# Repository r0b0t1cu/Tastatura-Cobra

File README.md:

# [RO] Tastatură Custom pentru Cobra & ZX Spectrum  

Acesta este un proiect open-source pentru o tastatură mecanică compatibilă cu computerul românesc **Cobra** și alte clone **ZX Spectrum**.
Tastatura a fost proiectată pentru a fi ușor de construit, utilizând componente accesibile.  

## Caracteristici  
- **Compatibilitate:** Cobra, ZX Spectrum și clone  
- **Conexiune:** Cablu panglică 2x10, conector montat pe partea inferioară a PCB-ului
- **Componente principale:**  
  - 59 Switch-uri mecanice cu 3 pini din plastic  
  - 3 x **IC CD4066**  
  - 29 x **diode BAT42**  
  - 12 x **rezistențe 100k**  
  - 1 x **condensator 10uF**  
  - 3 x **condensator 100nF**  
  - 1 x **conector 2x10 pini**  
  - optional - 1 x **conector 2x4 pini**
- **Funcționalitate extinsă:**
  - Taste speciale pentru CP/M pe Cobra
  - Taste separate pentru: del, cursor, caps lock, edit, extended mode, "." (punct), "," (virgula), ":" (doua puncte)

## Instalare și Conectare  
1. **Montaj PCB:** Conectorul cablului panglică **trebuie montat pe partea inferioară** a PCB-ului.  
2. **Pentru Cobra:** Se conectează direct la interfața tastaturii.  
3. **Pentru ZX Spectrum și clone:** Se identifică manual liniile și coloanele din matrice și se ajustează conexiunile corespunzător. 
4. Tastatura este gândită să se potrivească pe carcasa de aici:
   - [https://www.z80-romania.ro/CoBra-64](https://www.z80-romania.ro/CoBra-64)  
   - Fișiere: [Download CoBra Case (ZIP)](https://www.z80-romania.ro/files/64/Carcasa%20CoBra%20-%20cobrasov.com%20(2024).zip?1708896374)

## Fișiere Disponibile  
- **Schematica și PCB:** Fișiere KiCad în folderul KICAD
- **Fișiere Gerber:** Pentru fabricarea PCB-ului în folderul PRODUCTION
- **BOM:** În folderul BOM
- **Grafica pentru stickere taste:** În folderul PDF
- **Schema:** În folderul PDF

## Surse și Mulțumiri  
Informațiile din acest proiect au fost inspirate și dezvoltate pe baza resurselor de la:  
- [cobrasov.com](https://cobrasov.com)  
- [CherryZXKeyboard](https://github.com/VlastimilWagner/CherryZXKeyboard)
- Și cu observații și input prețios de la [svpantazi](https://github.com/svpantazi)  

## Licență  
Acest proiect este **complet liber** pentru oricine dorește să-l folosească, modifice sau îmbunătățească.

# [EN] Custom Keyboard for Cobra & ZX Spectrum  

This is an open-source project for a mechanical keyboard compatible with the Romanian **Cobra** computer and other **ZX Spectrum clones**.  
The keyboard is designed to be easy to build, using readily available components.  

## Features  
- **Compatibility:** Cobra, ZX Spectrum, and clones  
- **Connection:** 2x10 ribbon cable, connector mounted on the **bottom side** of the PCB  
- **Main components:**  
  - 59 **mechanical switches** (3-pin plastic)  
  - 3 x **IC CD4066**  
  - 29 x **BAT42 diodes**  
  - 12 x **100k resistors**  
  - 1 x **10µF capacitor**  
  - 3 x **100nF capacitors**  
  - 1 x **2x10-pin connector**  
  - Optional: 1 x **2x4-pin connector**  
- **Extended functionality:**  
  - Special keys for CP/M on Cobra  
  - Separate keys for: Delete, Cursor, Caps Lock, Edit, Extended Mode, ".", ",", ":"  

## Installation & Connection  
1. **PCB Assembly:** The ribbon cable **must be mounted on the bottom side** of the PCB.  
2. **For Cobra:** Connects directly to the keyboard interface.  
3. **For ZX Spectrum and clones:** Manually identify the matrix rows and columns and adjust the connections accordingly.  
4. The keyboard is designed to fit in the case from:  
   - [https://www.z80-romania.ro/CoBra-64](https://www.z80-romania.ro/CoBra-64)  
   - Case files: [Download CoBra Case (ZIP)](https://www.z80-romania.ro/files/64/Carcasa%20CoBra%20-%20cobrasov.com%20(2024).zip?1708896374)

## Available Files  
- **Schematics & PCB:** KiCad files in the **KICAD** folder  
- **Gerber Files:** For PCB fabrication in the **PRODUCTION** folder  
- **BOM (Bill of Materials):** Located in the **BOM** folder  
- **Keycap Sticker Graphics:** In the **PDF** folder  
- **Schematic Diagram:** In the **PDF** folder  

## Sources & Acknowledgments  
This project was inspired and developed using information from:  
- [cobrasov.com](https://cobrasov.com)  
- [CherryZXKeyboard](https://github.com/VlastimilWagner/CherryZXKeyboard)  
- With valuable insights and feedback from [svpantazi](https://github.com/svpantazi)  

## License  
This project is **completely free** for anyone to use, modify, or improve.

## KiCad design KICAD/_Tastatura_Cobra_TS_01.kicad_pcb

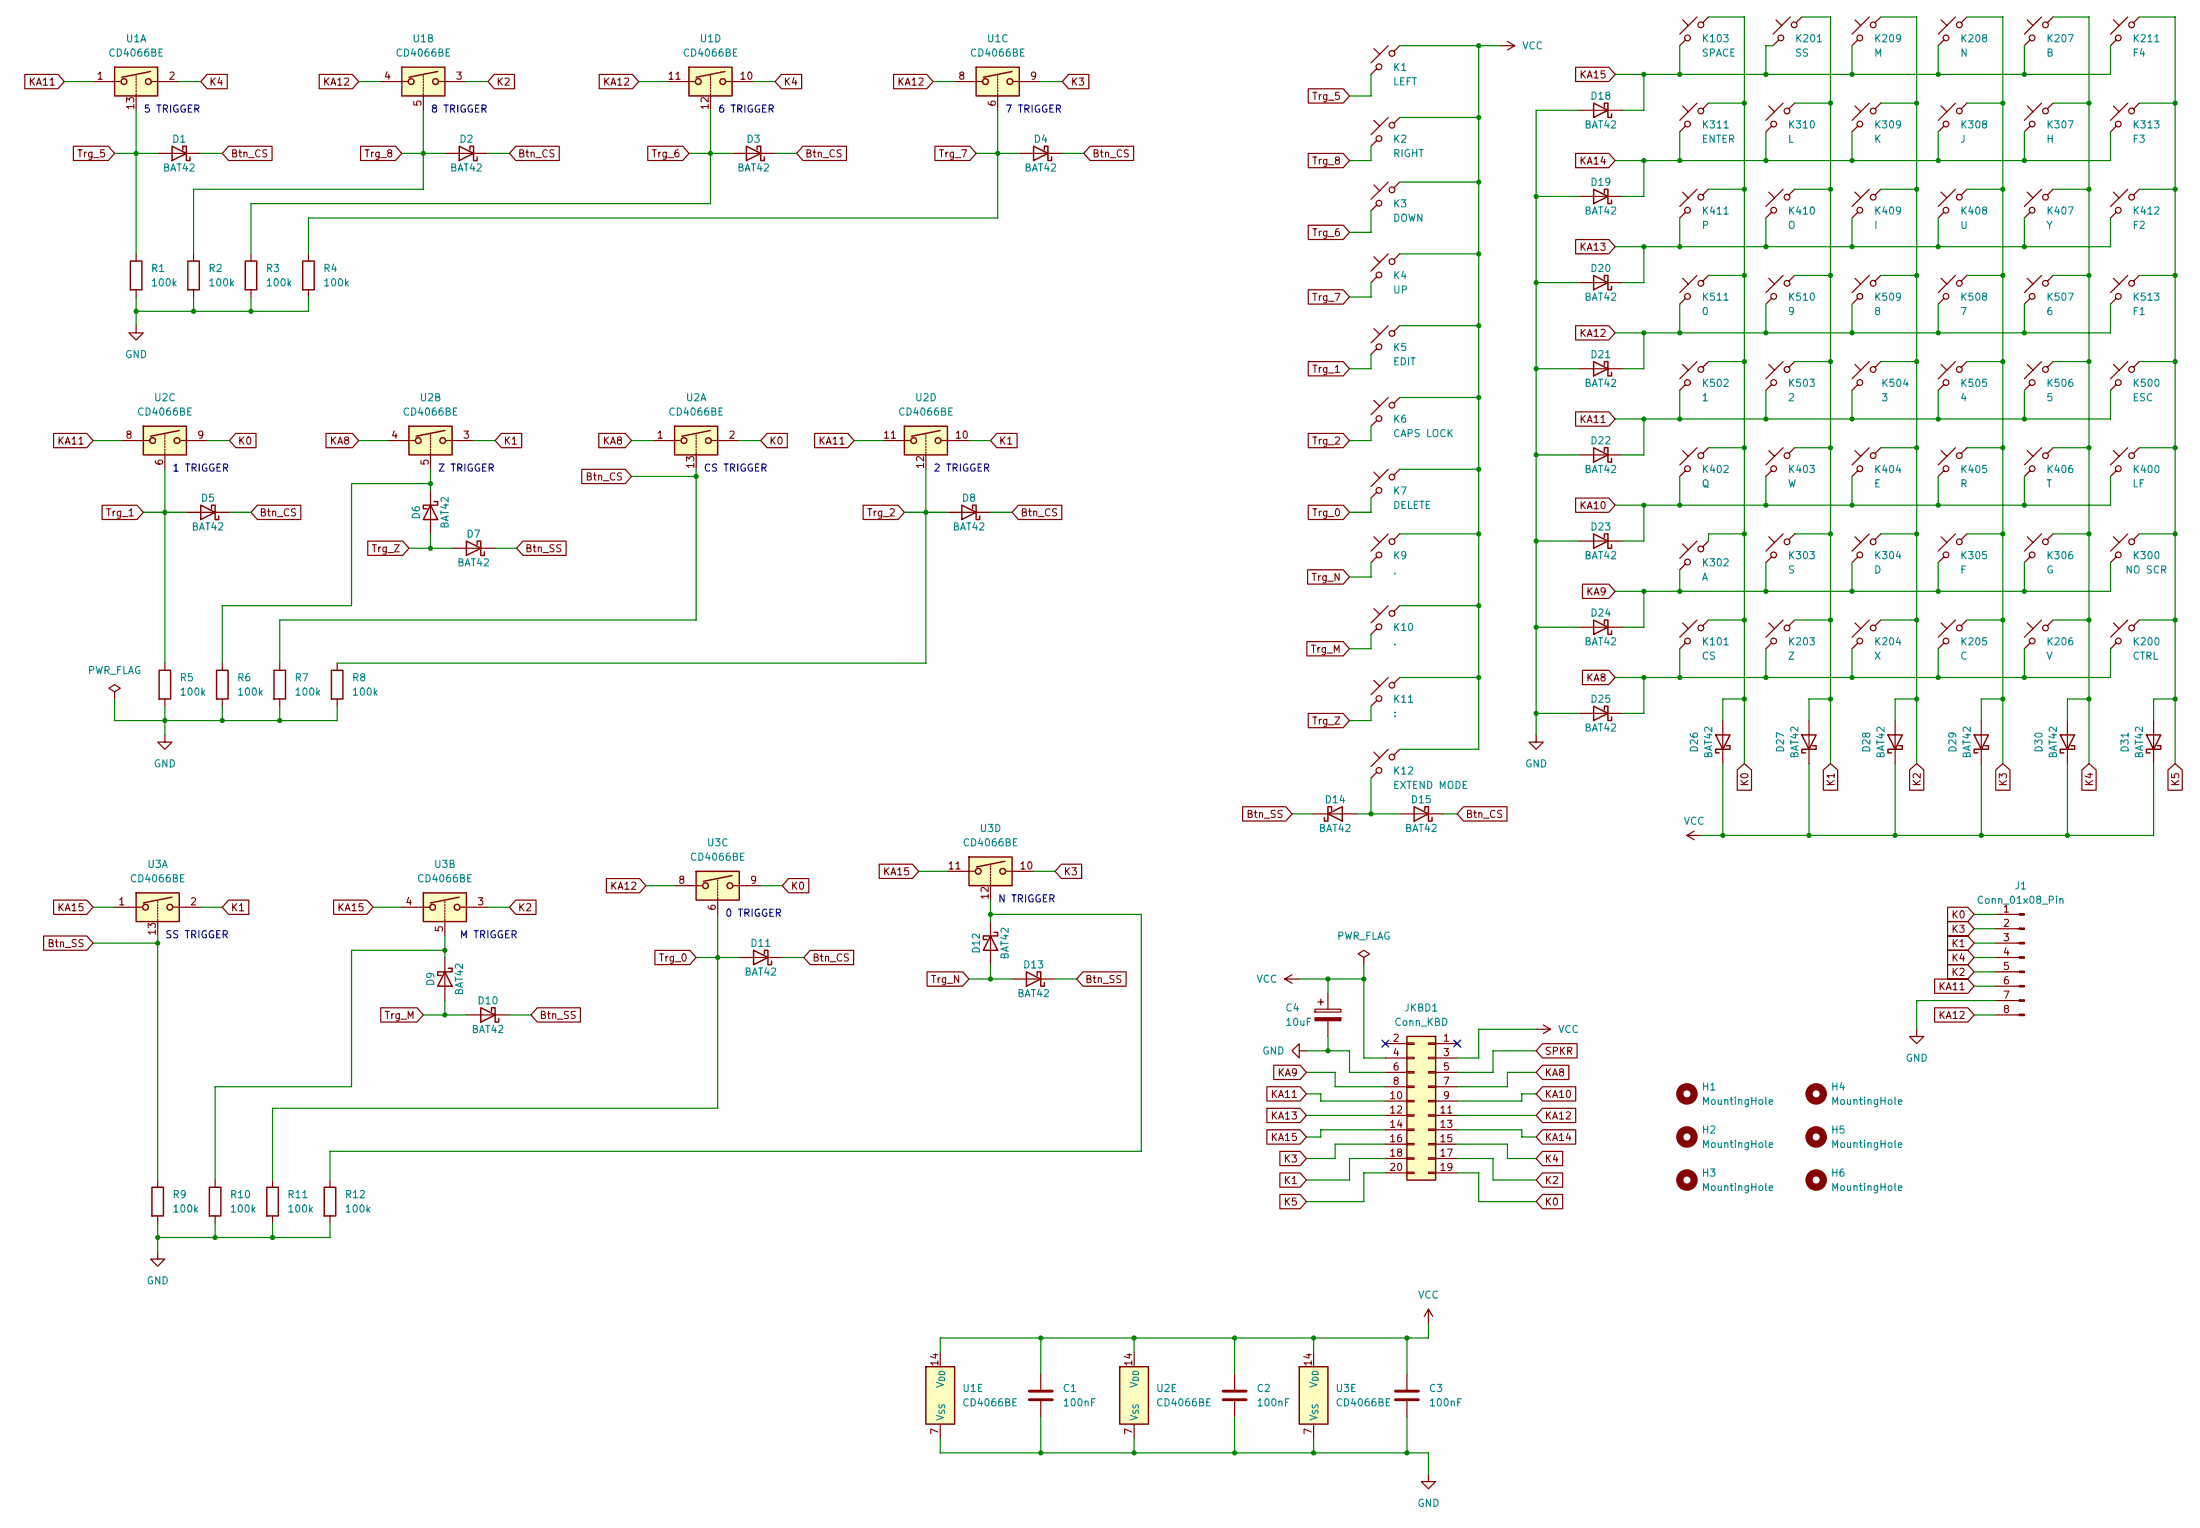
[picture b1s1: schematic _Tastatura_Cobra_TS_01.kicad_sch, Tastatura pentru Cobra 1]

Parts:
C1, C2, C3: 100nF; C_Disc_D4.3mm_W1.9mm_P5.00mm
C4: 10uF; CP_Radial_D5.0mm_P2.50mm
D1, D2, D3, D4, D5, D6, D7, D8, D9, D10, D11, D12, D13, D14, D15, D18, D19, D20, D21, D22, D23, D24, D25, D26, D27, D28, D29, D30, D31: BAT42; D_DO-35_SOD27_P7.62mm_Horizontal
H1, H2, H3, H4, H5, H6: MountingHole; MountingHole_3.2mm_M3_Pad_TopBottom
J1: Conn_01x08_Pin; PinHeader_2x04_P2.54mm_Horizontal
JKBD1: Conn_KBD; IDC-Header_2x10_P2.54mm_Horizontal
K1: LEFT; SW_Cherry_MX_1.00u_PCB
K2: RIGHT; SW_Cherry_MX_1.00u_PCB
K3: DOWN; SW_Cherry_MX_1.25u_PCB
K4: UP; SW_Cherry_MX_1.25u_PCB
K5: EDIT; SW_Cherry_MX_1.25u_PCB
K6: CAPS LOCK; SW_Cherry_MX_1.25u_PCB
K7: DELETE; SW_Cherry_MX_1.25u_PCB
K9: ,; SW_Cherry_MX_1.25u_PCB
K10: .; SW_Cherry_MX_1.00u_PCB
K11: :; SW_Cherry_MX_1.00u_PCB
K12: EXTEND MODE; SW_Cherry_MX_1.00u_PCB
K101: CS; SW_Cherry_MX_2.00u_PCB
K103: SPACE; SW_Cherry_MX_6.25u_PCB
K200: CTRL; SW_Cherry_MX_1.00u_PCB
K201: SS; SW_Cherry_MX_2.00u_PCB
K203: Z; SW_Cherry_MX_1.00u_PCB
K204: X; SW_Cherry_MX_1.00u_PCB
K205: C; SW_Cherry_MX_1.00u_PCB
K206: V; SW_Cherry_MX_1.00u_PCB
K207: B; SW_Cherry_MX_1.00u_PCB
K208: N; SW_Cherry_MX_1.00u_PCB
K209: M; SW_Cherry_MX_1.00u_PCB
K211: F4; SW_Cherry_MX_1.00u_PCB
K300: NO SCR; SW_Cherry_MX_1.00u_PCB
K302: A; SW_Cherry_MX_1.00u_PCB
K303: S; SW_Cherry_MX_1.00u_PCB
K304: D; SW_Cherry_MX_1.00u_PCB
K305: F; SW_Cherry_MX_1.00u_PCB
K306: G; SW_Cherry_MX_1.00u_PCB
K307: H; SW_Cherry_MX_1.00u_PCB
K308: J; SW_Cherry_MX_1.00u_PCB
K309: K; SW_Cherry_MX_1.00u_PCB
K310: L; SW_Cherry_MX_1.00u_PCB
K311: ENTER; SW_Cherry_MX_1.75u_PCB
K313: F3; SW_Cherry_MX_1.00u_PCB
K400: LF; SW_Cherry_MX_1.00u_PCB
K402: Q; SW_Cherry_MX_1.00u_PCB
K403: W; SW_Cherry_MX_1.00u_PCB
K404: E; SW_Cherry_MX_1.00u_PCB
K405: R; SW_Cherry_MX_1.00u_PCB
K406: T; SW_Cherry_MX_1.00u_PCB
K407: Y; SW_Cherry_MX_1.00u_PCB
K408: U; SW_Cherry_MX_1.00u_PCB
K409: I; SW_Cherry_MX_1.00u_PCB
K410: O; SW_Cherry_MX_1.00u_PCB
K411: P; SW_Cherry_MX_1.00u_PCB
K412: F2; SW_Cherry_MX_1.00u_PCB
K500: ESC; SW_Cherry_MX_1.00u_PCB
K502: 1; SW_Cherry_MX_1.00u_PCB
K503: 2; SW_Cherry_MX_1.00u_PCB
K504: 3; SW_Cherry_MX_1.00u_PCB
K505: 4; SW_Cherry_MX_1.00u_PCB
K506: 5; SW_Cherry_MX_1.00u_PCB
K507: 6; SW_Cherry_MX_1.00u_PCB
K508: 7; SW_Cherry_MX_1.00u_PCB
K509: 8; SW_Cherry_MX_1.00u_PCB
K510: 9; SW_Cherry_MX_1.00u_PCB
K511: 0; SW_Cherry_MX_1.00u_PCB
K513: F1; SW_Cherry_MX_1.00u_PCB
R1, R2, R3, R4, R5, R6, R7, R8, R9, R10, R11, R12: 100k; R_Axial_DIN0207_L6.3mm_D2.5mm_P7.62mm_Horizontal
U1, U2, U3: CD4066BE; DIP-14_W7.62mm

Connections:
Btn_CS: D1.1 (K), D2.1 (K), D3.1 (K), D4.1 (K), D5.1 (K), D8.1 (K), D11.1 (K), D15.1 (K), R7.1, U2.13
Btn_SS: D7.1 (K), D10.1 (K), D13.1 (K), D14.1 (K), R9.1, U3.13
GND: C1.2, C2.2, C3.2, C4.2, D18.2 (A), D19.2 (A), D20.2 (A), D21.2 (A), D22.2 (A), D23.2 (A), D24.2 (A), D25.2 (A), J1.7, JKBD1.6, R1.2, R2.2, R3.2, R4.2, R5.2, R6.2, R7.2, R8.2, R9.2, R10.2, R11.2, R12.2, U1.7 (V_{SS}), U2.7 (V_{SS}), U3.7 (V_{SS})
K0: D26.2 (A), J1.1, JKBD1.19, K101.2, K103.2, K302.2, K311.2, K402.2, K411.2, K502.2, K511.2, U2.2, U2.9, U3.9
K1: D27.2 (A), J1.3, JKBD1.18, K201.2, K203.2, K303.2, K310.2, K403.2, K410.2, K503.2, K510.2, U2.3, U2.10, U3.2
K2: D28.2 (A), J1.5, JKBD1.17, K204.2, K209.2, K304.2, K309.2, K404.2, K409.2, K504.2, K509.2, U1.3, U3.3
K3: D29.2 (A), J1.2, JKBD1.16, K205.2, K208.2, K305.2, K308.2, K405.2, K408.2, K505.2, K508.2, U1.9, U3.10
K4: D30.2 (A), J1.4, JKBD1.15, K206.2, K207.2, K306.2, K307.2, K406.2, K407.2, K506.2, K507.2, U1.2, U1.10
K5: D31.2 (A), JKBD1.20, K200.2, K211.2, K300.2, K313.2, K400.2, K412.2, K500.2, K513.2
KA8: D25.1 (K), JKBD1.7, K101.1, K200.1, K203.1, K204.1, K205.1, K206.1, U2.1, U2.4
KA9: D24.1 (K), JKBD1.8, K300.1, K302.1, K303.1, K304.1, K305.1, K306.1
KA10: D23.1 (K), JKBD1.9, K400.1, K402.1, K403.1, K404.1, K405.1, K406.1
KA11: D22.1 (K), J1.6, JKBD1.10, K500.1, K502.1, K503.1, K504.1, K505.1, K506.1, U1.1, U2.8, U2.11
KA12: D21.1 (K), J1.8, JKBD1.11, K507.1, K508.1, K509.1, K510.1, K511.1, K513.1, U1.4, U1.8, U1.11, U3.8
KA13: D20.1 (K), JKBD1.12, K407.1, K408.1, K409.1, K410.1, K411.1, K412.1
KA14: D19.1 (K), JKBD1.13, K307.1, K308.1, K309.1, K310.1, K311.1, K313.1
KA15: D18.1 (K), JKBD1.14, K103.1, K201.1, K207.1, K208.1, K209.1, K211.1, U3.1, U3.4, U3.11
unnamed: D6.1 (K), R6.1, U2.5
unnamed: D9.1 (K), R10.1, U3.5
unnamed: D12.1 (K), R12.1, U3.12
unnamed: D14.2 (A), D15.2 (A), K12.2
SPKR: JKBD1.5
Trg_0: D11.2 (A), K7.2, R11.1, U3.6
Trg_1: D5.2 (A), K5.2, R5.1, U2.6
Trg_2: D8.2 (A), K6.2, R8.1, U2.12
Trg_5: D1.2 (A), K1.2, R1.1, U1.13
Trg_6: D3.2 (A), K3.2, R3.1, U1.12
Trg_7: D4.2 (A), K4.2, R4.1, U1.6
Trg_8: D2.2 (A), K2.2, R2.1, U1.5
Trg_M: D9.2 (A), D10.2 (A), K10.2
Trg_N: D12.2 (A), D13.2 (A), K9.2
Trg_Z: D6.2 (A), D7.2 (A), K11.2
VCC: C1.1, C2.1, C3.1, C4.1, D26.1 (K), D27.1 (K), D28.1 (K), D29.1 (K), D30.1 (K), D31.1 (K), JKBD1.3, JKBD1.4, K1.1, K2.1, K3.1, K4.1, K5.1, K6.1, K7.1, K9.1, K10.1, K11.1, K12.1, U1.14 (V_{DD}), U2.14 (V_{DD}), U3.14 (V_{DD})

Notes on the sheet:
1 TRIGGER
7 TRIGGER
0 TRIGGER
SS TRIGGER
8 TRIGGER
6 TRIGGER
2 TRIGGER
Z TRIGGER
CS TRIGGER
5 TRIGGER
N TRIGGER
M TRIGGER

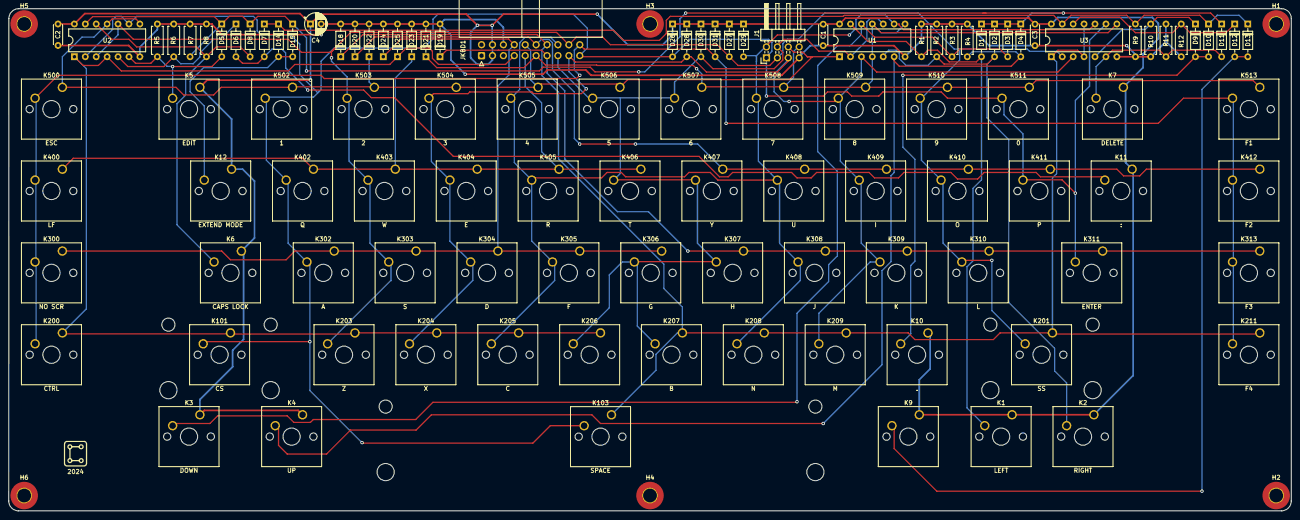
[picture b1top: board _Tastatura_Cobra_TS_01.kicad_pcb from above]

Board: 2 copper layers, 298.4 x 116.8 mm, 115 parts (0 on the bottom side), 32 nets.

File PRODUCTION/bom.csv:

Designator,Footprint,Quantity,Value,LCSC Part #
"C1, C2, C3",C_Disc_D4.3mm_W1.9mm_P5.00mm,3,100nF,
C4,CP_Radial_D5.0mm_P2.50mm,1,10uF,
"D1, D10, D11, D12, D13, D14, D15, D18, D19, D2, D20, D21, D22, D23, D24, D25, D26, D27, D28, D29, D3, D30, D31, D4, D5, D6, D7, D8, D9",D_DO-35_SOD27_P7.62mm_Horizontal,29,BAT42,
J1,PinHeader_2x04_P2.54mm_Horizontal,1,Conn_01x08_Pin,
JKBD1,IDC-Header_2x10_P2.54mm_Horizontal,1,Conn_KBD,
K1,SW_Cherry_MX_1.00u_PCB,1,LEFT,
K10,SW_Cherry_MX_1.00u_PCB,1,.,
K101,SW_Cherry_MX_2.00u_PCB,1,CS,
K103,SW_Cherry_MX_6.25u_PCB,1,SPACE,
K11,SW_Cherry_MX_1.00u_PCB,1,:,
K12,SW_Cherry_MX_1.00u_PCB,1,EXTEND MODE,
K2,SW_Cherry_MX_1.00u_PCB,1,RIGHT,
K200,SW_Cherry_MX_1.00u_PCB,1,CTRL,
K201,SW_Cherry_MX_2.00u_PCB,1,SS,
K203,SW_Cherry_MX_1.00u_PCB,1,Z,
K204,SW_Cherry_MX_1.00u_PCB,1,X,
K205,SW_Cherry_MX_1.00u_PCB,1,C,
K206,SW_Cherry_MX_1.00u_PCB,1,V,
K207,SW_Cherry_MX_1.00u_PCB,1,B,
K208,SW_Cherry_MX_1.00u_PCB,1,N,
K209,SW_Cherry_MX_1.00u_PCB,1,M,
K211,SW_Cherry_MX_1.00u_PCB,1,F4,
K3,SW_Cherry_MX_1.25u_PCB,1,DOWN,
K300,SW_Cherry_MX_1.00u_PCB,1,NO SCR,
K302,SW_Cherry_MX_1.00u_PCB,1,A,
K303,SW_Cherry_MX_1.00u_PCB,1,S,
K304,SW_Cherry_MX_1.00u_PCB,1,D,
K305,SW_Cherry_MX_1.00u_PCB,1,F,
K306,SW_Cherry_MX_1.00u_PCB,1,G,
K307,SW_Cherry_MX_1.00u_PCB,1,H,
K308,SW_Cherry_MX_1.00u_PCB,1,J,
K309,SW_Cherry_MX_1.00u_PCB,1,K,
K310,SW_Cherry_MX_1.00u_PCB,1,L,
K311,SW_Cherry_MX_1.75u_PCB,1,ENTER,
K313,SW_Cherry_MX_1.00u_PCB,1,F3,
K4,SW_Cherry_MX_1.25u_PCB,1,UP,
K400,SW_Cherry_MX_1.00u_PCB,1,LF,
K402,SW_Cherry_MX_1.00u_PCB,1,Q,
K403,SW_Cherry_MX_1.00u_PCB,1,W,
K404,SW_Cherry_MX_1.00u_PCB,1,E,
K405,SW_Cherry_MX_1.00u_PCB,1,R,
K406,SW_Cherry_MX_1.00u_PCB,1,T,
K407,SW_Cherry_MX_1.00u_PCB,1,Y,
K408,SW_Cherry_MX_1.00u_PCB,1,U,
K409,SW_Cherry_MX_1.00u_PCB,1,I,
K410,SW_Cherry_MX_1.00u_PCB,1,O,
K411,SW_Cherry_MX_1.00u_PCB,1,P,
K412,SW_Cherry_MX_1.00u_PCB,1,F2,
K5,SW_Cherry_MX_1.25u_PCB,1,EDIT,
K500,SW_Cherry_MX_1.00u_PCB,1,ESC,
K502,SW_Cherry_MX_1.00u_PCB,1,1,
K503,SW_Cherry_MX_1.00u_PCB,1,2,
K504,SW_Cherry_MX_1.00u_PCB,1,3,
K505,SW_Cherry_MX_1.00u_PCB,1,4,
K506,SW_Cherry_MX_1.00u_PCB,1,5,
K507,SW_Cherry_MX_1.00u_PCB,1,6,
K508,SW_Cherry_MX_1.00u_PCB,1,7,
K509,SW_Cherry_MX_1.00u_PCB,1,8,
K510,SW_Cherry_MX_1.00u_PCB,1,9,
K511,SW_Cherry_MX_1.00u_PCB,1,0,
K513,SW_Cherry_MX_1.00u_PCB,1,F1,
K6,SW_Cherry_MX_1.25u_PCB,1,CAPS LOCK,
K7,SW_Cherry_MX_1.25u_PCB,1,DELETE,
K9,SW_Cherry_MX_1.25u_PCB,1,",",
"R1, R10, R11, R12, R2, R3, R4, R5, R6, R7, R8, R9",R_Axial_DIN0207_L6.3mm_D2.5mm_P7.62mm_Horizontal,12,100k,
"U1, U2, U3",DIP-14_W7.62mm,3,CD4066BE,
